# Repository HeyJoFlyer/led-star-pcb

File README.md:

# LED Star PCB and Panelized Version

## Overview
This repository contains the design files for an open-source LED star printed circuit board (PCB) and a panelized version for ease of production. The PCB is designed to accommodate a single 1W LED for optimal heatsinking and simplified wire connections. This project was made with KiCad and the outline was made using Inkscape.

## Features
- Single 1 / 3W LED mounting footprint
- Terminal points for easy wire connections
- Open-source design for customization and improvements, even for comercial use
- An alternative to the expensive pre-made pcbs
- 100*100mm panelized version for cheaper manufacturing
- square and star shaped pcbs (traced from scan of real star pcb)

## Versions:
- Scanned from original pcb:

- Square pcb:

- Panelized Square pcb:

## Usage
### LED Star PCB
1. Manufacture the PCB using the provided Gerber files, you need to choose the aluminum pcb (I got mine free of charge thanks to [PCBWay](https://www.pcbway.com/)).
1. Mount the LED onto the designated footprint.
1. Connect wires to the terminals for power supply as indicated.

### Panelized Version (cheaper!)
1. Follow the same steps as for the LED Star PCB but using the panelized Gerber files, you need to choose the aluminum pcb.
1. Sparate individual PCBs from the panel after manufacturing (at the score lines).
1. Assemble each individual PCB as instructed for the LED Star PCB.

### Library
If you want to edit the pcb you will need to install the provided library `library.pretty` for the solder connections.

## License
This project is licensed under the [MIT License](LICENSE).

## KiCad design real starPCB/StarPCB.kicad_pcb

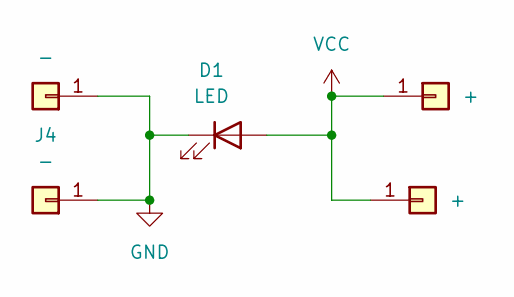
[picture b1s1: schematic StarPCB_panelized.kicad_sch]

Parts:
D1: LED; LED_1W_3W_R8
J1, J2: +; Connector_WireSolderWirePad_1x01_SMD_2x4mm
J4, J5: -; Connector_WireSolderWirePad_1x01_SMD_2x4mm

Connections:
GND: D1.1 (K), J4.1, J5.1
VCC: D1.2 (A), J1.1, J2.1

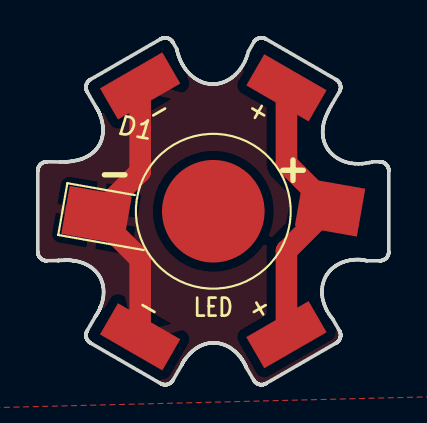
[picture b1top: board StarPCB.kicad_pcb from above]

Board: 2 copper layers, 19.5 x 19.3 mm, 5 parts (0 on the bottom side), 2 nets.

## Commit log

2023-12-19 new trace using shapes
2024-01-06 Added real photos
